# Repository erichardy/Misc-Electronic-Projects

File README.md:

# Misc-Electronic-Projects
Electronic circuits and projects I am working on as a hobbyist

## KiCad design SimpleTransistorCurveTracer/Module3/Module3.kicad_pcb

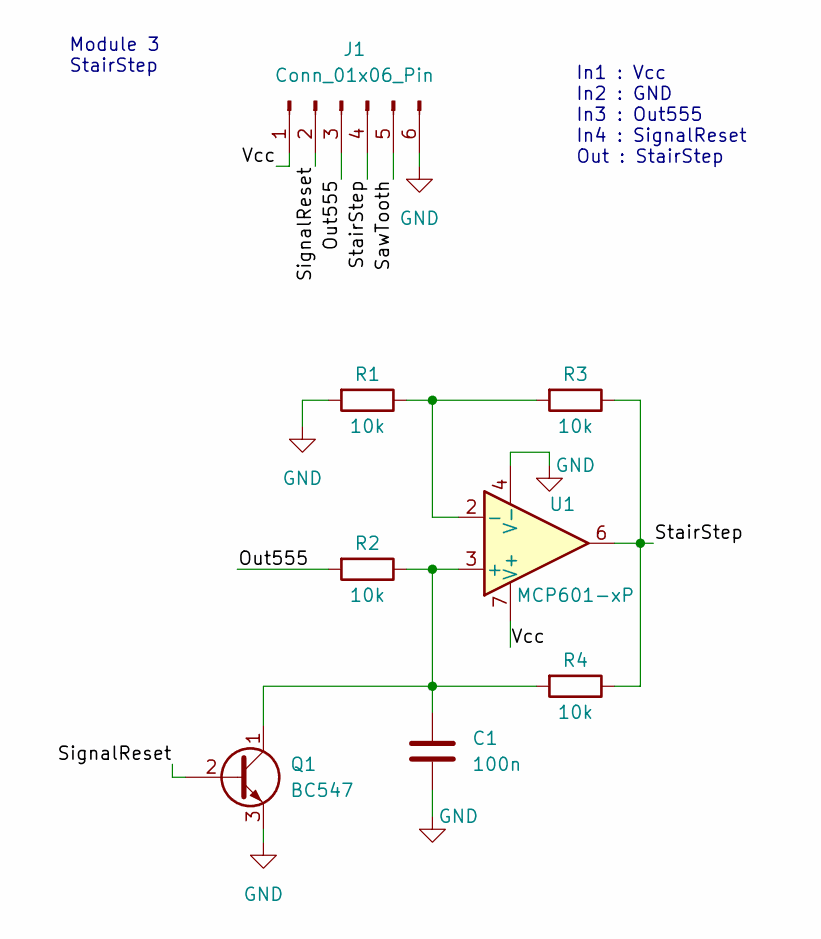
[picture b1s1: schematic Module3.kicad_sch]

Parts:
C1: 100n; C_Disc_D7.5mm_W2.5mm_P5.00mm
J1: Conn_01x06_Pin; PinHeader_1x06_P2.54mm_Horizontal
Q1: BC547; TO-92_Inline
R1, R2, R3, R4: 10k; R_Axial_DIN0411_L9.9mm_D3.6mm_P15.24mm_Horizontal
U1: MCP601-xP; DIP-8_W7.62mm

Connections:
/Out555: J1.3, R2.2
/SawTooth: J1.5
/SignalReset: J1.2, Q1.2 (B)
/StairStep: J1.4, R3.1, R4.1, U1.6
/Vcc: J1.1, U1.7 (V+)
GND: C1.2, J1.6, Q1.3 (E), R1.2, U1.4 (V-)
unnamed: C1.1, Q1.1 (C), R2.1, R4.2, U1.3 (+)
unnamed: R1.1, R3.2, U1.2 (-)

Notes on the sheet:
Module 3 StairStep
In1 : Vcc In2 : GND In3 : Out555 In4 : SignalReset Out : StairStep

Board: 2 copper layers, 8 parts (0 on the bottom side), 7 nets, no tracks yet.

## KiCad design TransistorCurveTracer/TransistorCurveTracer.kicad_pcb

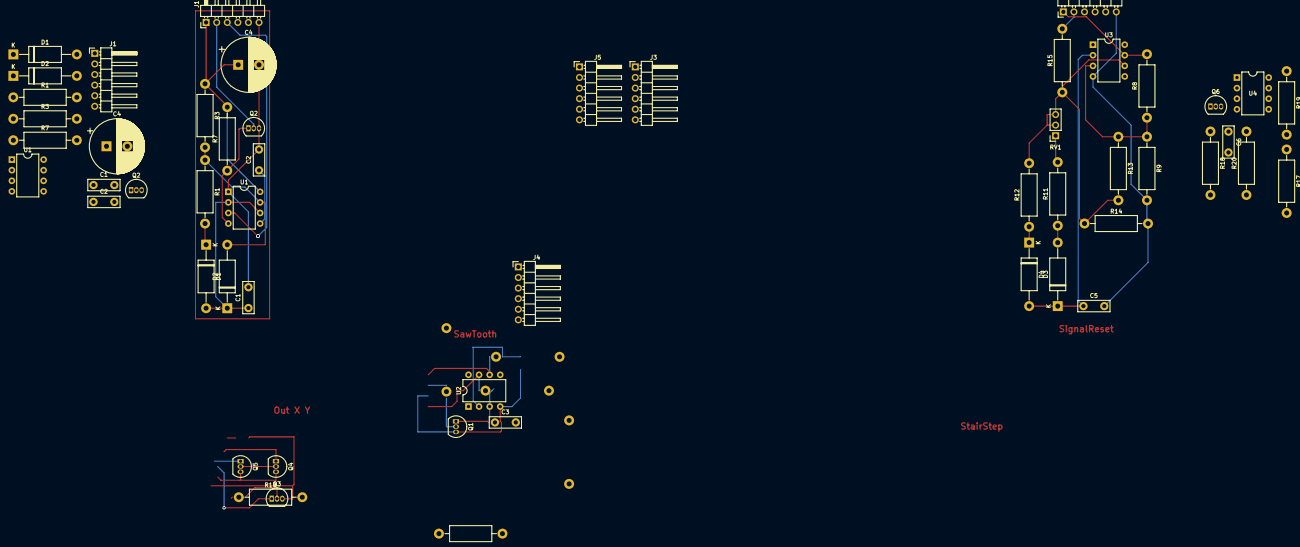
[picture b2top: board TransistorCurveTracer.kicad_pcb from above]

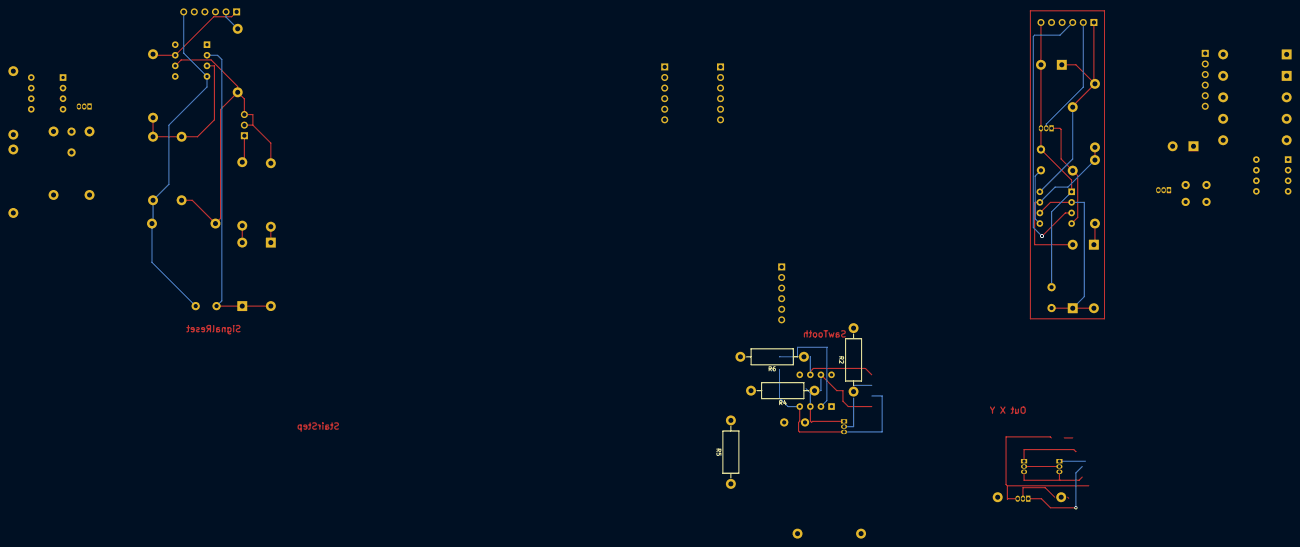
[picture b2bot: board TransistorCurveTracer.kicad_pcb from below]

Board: 2 copper layers, 57 parts (4 on the bottom side), 25 nets.

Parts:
C1, C1#2, C2, C2#2, C3: 10n; C_Disc_D7.5mm_W2.5mm_P5.00mm
C4, C4#2: 47u; CP_Radial_D13.0mm_P5.00mm
C5, C6: 100n; C_Disc_D7.5mm_W2.5mm_P5.00mm
D1, D1#2, D2, D2#2, D3, D4: 1N4148; D_DO-15_P15.24mm_Horizontal
J1, J1#2, J2, J3, J4, J5: Conn_01x06_Pin; PinHeader_1x06_P2.54mm_Horizontal
Q1, Q2, Q2#2, Q6: BC547; TO-92_Inline
Q3: DUT; TO-92_Inline
Q4, Q5: 2N2907; TO-92_Inline
R1, R1#2, R12: 39k; R_Axial_DIN0411_L9.9mm_D3.6mm_P15.24mm_Horizontal
R2, R5: 3.9k; R_Axial_DIN0411_L9.9mm_D3.6mm_P15.24mm_Horizontal
R3, R3#2: 4.7k; R_Axial_DIN0411_L9.9mm_D3.6mm_P15.24mm_Horizontal
R4, R6, R7, R7#2, R17, R18, R19, R20: 10k; R_Axial_DIN0411_L9.9mm_D3.6mm_P15.24mm_Horizontal
R8, R9: 33k; R_Axial_DIN0411_L9.9mm_D3.6mm_P15.24mm_Horizontal
R10: 470k; R_Axial_DIN0411_L9.9mm_D3.6mm_P15.24mm_Horizontal
R11: 1k; R_Axial_DIN0411_L9.9mm_D3.6mm_P15.24mm_Horizontal
R13: 15k; R_Axial_DIN0411_L9.9mm_D3.6mm_P15.24mm_Horizontal
R14: 6.8k; R_Axial_DIN0411_L9.9mm_D3.6mm_P15.24mm_Horizontal
R15: 8.2k; R_Axial_DIN0411_L9.9mm_D3.6mm_P15.24mm_Horizontal
R16: 270k; R_Axial_DIN0411_L9.9mm_D3.6mm_P15.24mm_Horizontal
RV1: 0-5k; PinSocket_1x03_P2.54mm_Vertical
U1, U1#2: NE555P; DIP-8_W7.62mm
U2, U3, U4: MCP601-xP; DIP-8_W7.62mm

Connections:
/Out555: J1.3, J1#2.3, J2.3, J3.3, J4.3, J5.3, R2.2, R18.2, U1.3 (Q), U1#2.3 (Q)
/Reset555: Q2.1 (C), Q2#2.1 (C), R7.1, R7#2.1, U1.4 (R), U1#2.4 (R)
/SawTooth: J1.5, J1#2.5, J2.5, J3.5, J4.5, J5.5, Q4.3 (E), Q5.3 (E), R6.1, U2.6
/SignalReset: J1.2, J1#2.2, J2.2, J3.2, J4.2, J5.2, Q2.2 (B), Q2#2.2 (B), Q6.2 (B), R15.2
/StairStep: J1.4, J1#2.4, J2.4, J3.4, J4.4, J5.4, R10.1, R19.1, R20.1, U4.6
/Vcc: C4.1, C4#2.1, J1.1, J1#2.1, J2.1, J3.1, J4.1, J5.1, R3.1, R3#2.1, R4.1, R7.2, R7#2.2, R8.2, U1.8 (VCC), U1#2.8 (VCC), U2.7 (V+), U3.7 (V+), U4.7 (V+)
/X: Q3.1 (C), Q4.1 (C), Q4.2 (B), Q5.2 (B)
/Y: Q5.1 (C), R16.1
GND: C1.2, C1#2.2, C2.2, C2#2.2, C3.2, C4.2, C4#2.2, C5.2, C6.2, J1.6, J1#2.6, J2.6, J3.6, J4.6, J5.6, Q1.3 (E), Q2.3 (E), Q2#2.3 (E), Q3.3 (E), Q6.3 (E), R5.2, R9.2, R14.2, R16.2, R17.2, U1.1 (GND), U1#2.1 (GND), U2.4 (V-), U3.4 (V-), U4.4 (V-)
unnamed: C1.1, C1#2.1, D1.2 (A), D1#2.2 (A), D2.1 (K), D2#2.1 (K), U1.2 (TR), U1.6 (THR), U1#2.2 (TR), U1#2.6 (THR)
unnamed: D1.1 (K), D1#2.1 (K), R1.2, R1#2.2
unnamed: D2.2 (A), D2#2.2 (A), R1.1, R1#2.1, R3.2, R3#2.2, U1.7 (DIS), U1#2.7 (DIS)
unnamed: D3.2 (A), R11.1
unnamed: C5.1, D3.1 (K), D4.2 (A), U3.2 (-)
unnamed: D4.1 (K), R12.1
unnamed: Q1.2 (B), R2.1
unnamed: C3.1, Q1.1 (C), R4.2, U2.3 (+)
unnamed: Q3.2 (B), R10.2
unnamed: C6.1, Q6.1 (C), R18.1, R20.2, U4.3 (+)
unnamed: R11.2, RV1.1
unnamed: R12.2, R13.2, R14.1, R15.1, RV1.2, RV1.3, U3.6
unnamed: C2.1, C2#2.1, U1.5 (CV), U1#2.5 (CV)
unnamed: R5.1, R6.2, U2.2 (-)
unnamed: R8.1, R9.1, R13.1, U3.3 (+)
unnamed: R17.1, R19.2, U4.2 (-)

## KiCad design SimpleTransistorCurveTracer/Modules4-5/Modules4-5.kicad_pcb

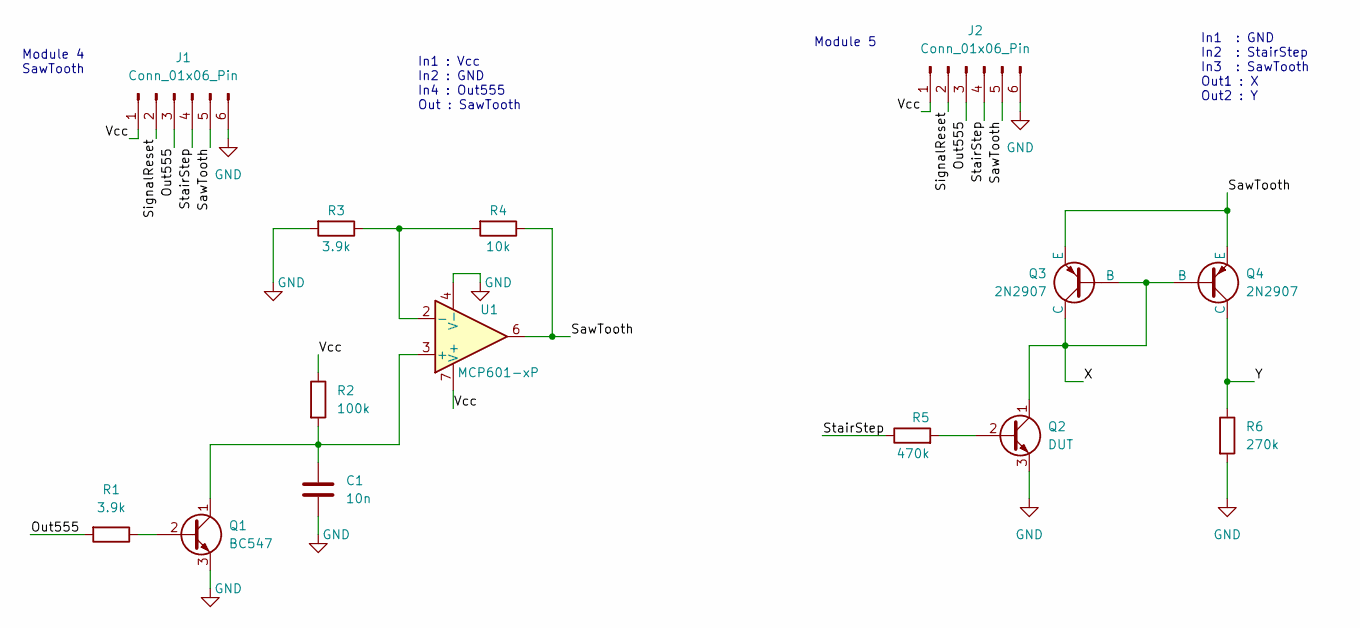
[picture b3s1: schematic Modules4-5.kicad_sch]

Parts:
C1: 10n; C_Disc_D7.5mm_W2.5mm_P5.00mm
J1, J2: Conn_01x06_Pin; PinHeader_1x06_P2.54mm_Horizontal
Q1: BC547; TO-92_Inline
Q2: DUT; TO-92_Inline
Q3, Q4: 2N2907; TO-92_Inline
R1, R3: 3.9k; R_Axial_DIN0411_L9.9mm_D3.6mm_P15.24mm_Horizontal
R2: 100k; R_Axial_DIN0411_L9.9mm_D3.6mm_P15.24mm_Horizontal
R4: 10k; R_Axial_DIN0411_L9.9mm_D3.6mm_P15.24mm_Horizontal
R5: 470k; R_Axial_DIN0411_L9.9mm_D3.6mm_P15.24mm_Horizontal
R6: 270k; R_Axial_DIN0411_L9.9mm_D3.6mm_P15.24mm_Horizontal
U1: MCP601-xP; DIP-8_W7.62mm

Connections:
/Out555: J1.3, J2.3, R1.2
/SawTooth: J1.5, J2.5, Q3.3 (E), Q4.3 (E), R4.1, U1.6
/SignalReset: J1.2, J2.2
/StairStep: J1.4, J2.4, R5.1
/Vcc: J1.1, J2.1, R2.1, U1.7 (V+)
/X: Q2.1 (C), Q3.1 (C), Q3.2 (B), Q4.2 (B)
/Y: Q4.1 (C), R6.1
GND: C1.2, J1.6, J2.6, Q1.3 (E), Q2.3 (E), R3.2, R6.2, U1.4 (V-)
unnamed: Q1.2 (B), R1.1
unnamed: C1.1, Q1.1 (C), R2.2, U1.3 (+)
unnamed: Q2.2 (B), R5.2
unnamed: R3.1, R4.2, U1.2 (-)

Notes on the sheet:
Module 5
Module 4 SawTooth
In1 : Vcc In2 : GND In4 : Out555 Out : SawTooth
In1 : GND In2 : StairStep In3 : SawTooth Out1 : X Out2 : Y

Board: 2 copper layers, 14 parts (0 on the bottom side), 12 nets, no tracks yet.

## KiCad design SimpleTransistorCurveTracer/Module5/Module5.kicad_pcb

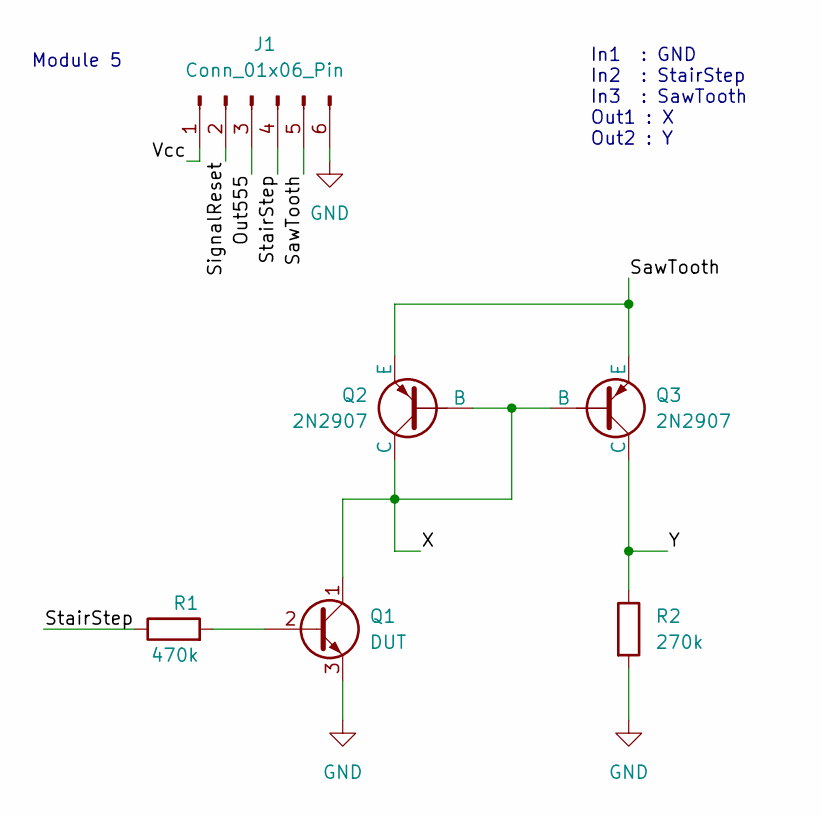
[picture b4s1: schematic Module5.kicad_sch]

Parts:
J1: Conn_01x06_Pin; PinHeader_1x06_P2.54mm_Horizontal
Q1: DUT; TO-92_Inline
Q2, Q3: 2N2907; TO-92_Inline
R1: 470k; R_Axial_DIN0411_L9.9mm_D3.6mm_P15.24mm_Horizontal
R2: 270k; R_Axial_DIN0411_L9.9mm_D3.6mm_P15.24mm_Horizontal

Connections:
/Out555: J1.3
/SawTooth: J1.5, Q2.3 (E), Q3.3 (E)
/SignalReset: J1.2
/StairStep: J1.4, R1.1
/Vcc: J1.1
/X: Q1.1 (C), Q2.1 (C), Q2.2 (B), Q3.2 (B)
/Y: Q3.1 (C), R2.1
GND: J1.6, Q1.3 (E), R2.2
unnamed: Q1.2 (B), R1.2

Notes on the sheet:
In1 : GND In2 : StairStep In3 : SawTooth Out1 : X Out2 : Y
Module 5

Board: 2 copper layers, 6 parts (0 on the bottom side), 6 nets, no tracks yet.

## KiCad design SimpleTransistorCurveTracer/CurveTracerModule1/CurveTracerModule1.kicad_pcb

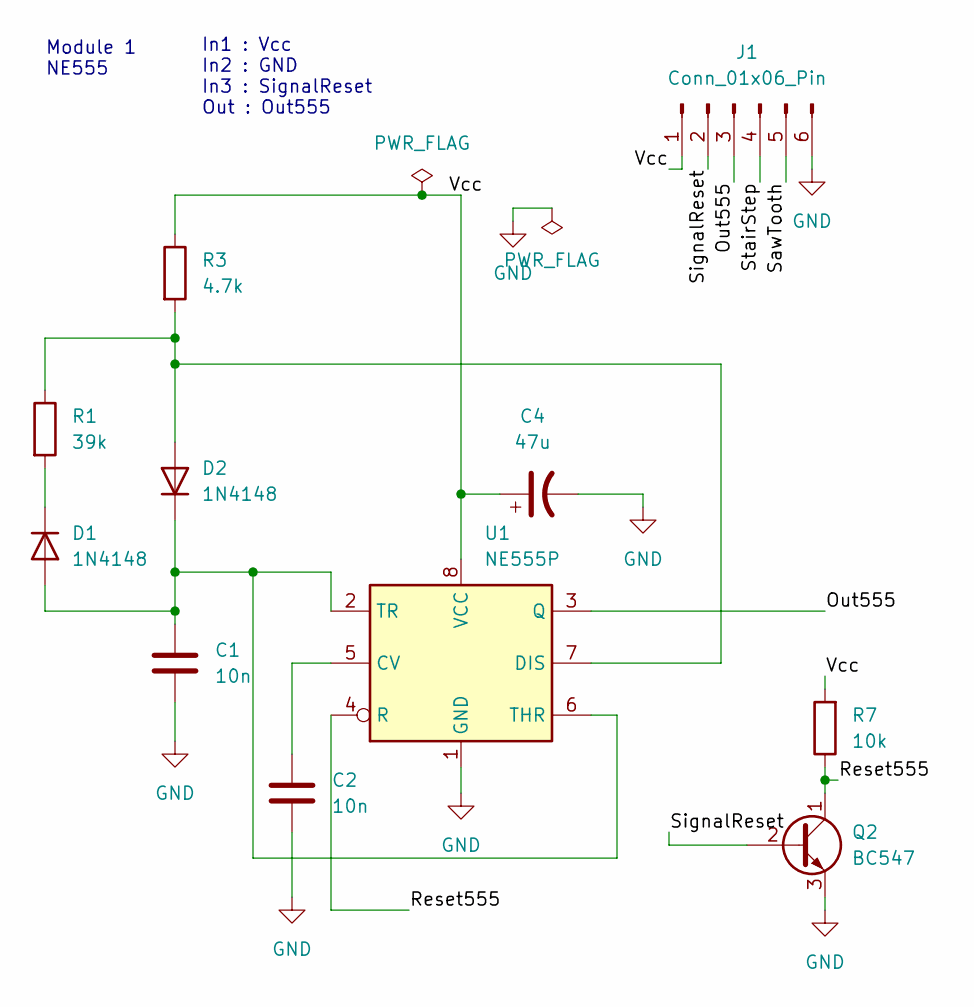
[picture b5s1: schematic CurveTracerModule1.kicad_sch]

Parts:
C1, C2: 10n; C_Disc_D7.5mm_W2.5mm_P5.00mm
C4: 47u; CP_Radial_D13.0mm_P5.00mm
D1, D2: 1N4148; D_DO-15_P15.24mm_Horizontal
J1: Conn_01x06_Pin; PinHeader_1x06_P2.54mm_Horizontal
Q2: BC547; TO-92_Inline
R1: 39k; R_Axial_DIN0411_L9.9mm_D3.6mm_P15.24mm_Horizontal
R3: 4.7k; R_Axial_DIN0411_L9.9mm_D3.6mm_P15.24mm_Horizontal
R7: 10k; R_Axial_DIN0411_L9.9mm_D3.6mm_P15.24mm_Horizontal
U1: NE555P; DIP-8_W7.62mm

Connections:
/Out555: J1.3, U1.3 (Q)
/Reset555: Q2.1 (C), R7.1, U1.4 (R)
/SawTooth: J1.5
/SignalReset: J1.2, Q2.2 (B)
/StairStep: J1.4
/Vcc: C4.1, J1.1, R3.1, R7.2, U1.8 (VCC)
GND: C1.2, C2.2, C4.2, J1.6, Q2.3 (E), U1.1 (GND)
unnamed: C1.1, D1.2 (A), D2.1 (K), U1.2 (TR), U1.6 (THR)
unnamed: D1.1 (K), R1.2
unnamed: D2.2 (A), R1.1, R3.2, U1.7 (DIS)
unnamed: C2.1, U1.5 (CV)

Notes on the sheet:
In1 : Vcc In2 : GND In3 : SignalReset Out : Out555
Module 1 NE555

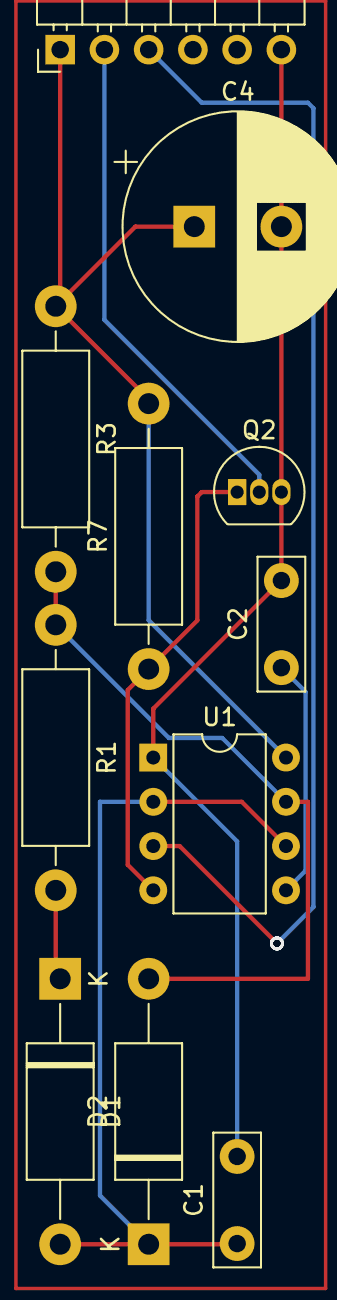
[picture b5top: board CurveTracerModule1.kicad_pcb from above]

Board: 2 copper layers, 11 parts (0 on the bottom side), 9 nets.

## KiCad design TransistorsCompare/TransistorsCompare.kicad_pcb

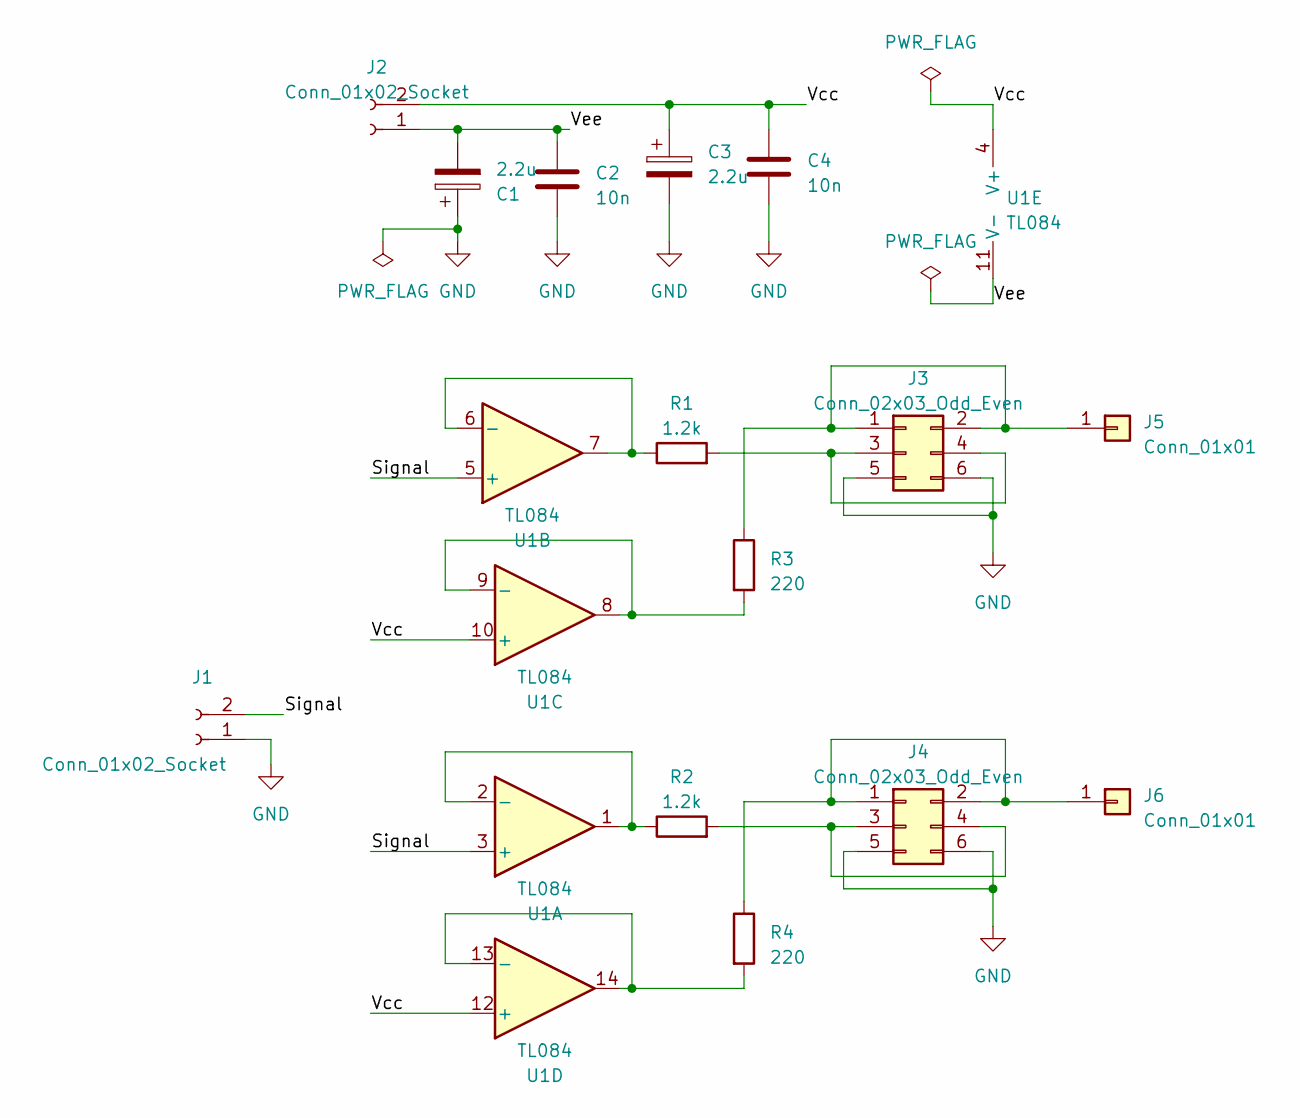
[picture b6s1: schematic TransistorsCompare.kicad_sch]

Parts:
C1, C3: 2.2u; C_Radial_D6.3mm_H5.0mm_P2.50mm
C2, C4: 10n; C_Disc_D5.0mm_W2.5mm_P2.50mm
J1, J2: Conn_01x02_Socket; PinSocket_1x02_P2.54mm_Vertical
J3, J4: Conn_02x03_Odd_Even; PinSocket_2x03_P2.54mm_Vertical
J5, J6: Conn_01x01; PinHeader_1x01_P2.54mm_Vertical
R1, R2: 1.2k; R_Axial_DIN0207_L6.3mm_D2.5mm_P10.16mm_Horizontal
R3, R4: 220; R_Axial_DIN0207_L6.3mm_D2.5mm_P10.16mm_Horizontal
U1: TL084; DIP-14_W7.62mm_Socket

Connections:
/Signal: J1.2, U1.3 (+), U1.5 (+)
/Vcc: C3.1, C4.1, J2.2, U1.4 (V+), U1.10 (+), U1.12 (+)
/Vee: C1.2, C2.1, J2.1, U1.11 (V-)
GND: C1.1, C2.2, C3.2, C4.2, J1.1, J3.5, J3.6, J4.5, J4.6
unnamed: J3.1, J3.2, J5.1, R3.1
unnamed: J3.3, J3.4, R1.2
unnamed: J4.1, J4.2, J6.1, R4.1
unnamed: J4.3, J4.4, R2.2
unnamed: R2.1, U1.1, U1.2 (-)
unnamed: R1.1, U1.6 (-), U1.7
unnamed: R3.2, U1.8, U1.9 (-)
unnamed: R4.2, U1.13 (-), U1.14

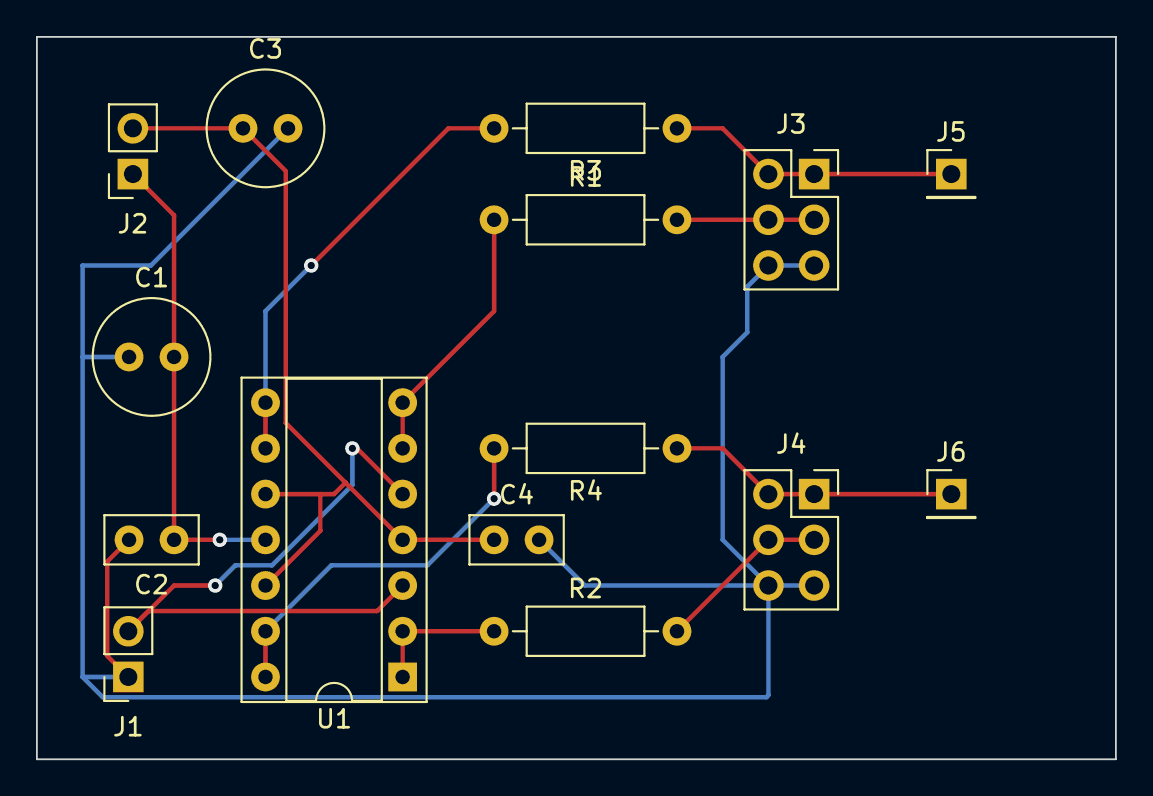
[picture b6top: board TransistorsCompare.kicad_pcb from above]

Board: 2 copper layers, 59.9 x 40.1 mm, 15 parts (0 on the bottom side), 12 nets.

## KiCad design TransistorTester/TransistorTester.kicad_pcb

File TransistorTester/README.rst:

One of my prefered electronic youtuber is w2aew (https://www.youtube.com/@w2aew) and this
circuit is from his video named :
 #281: Bipolar Transistor Switching Time Measurement
 (https://www.youtube.com/watch?v=XgSKLsWAWGs&ab_channel=w2aew)

A friend of mine gave me a lot of parts including transistors and I plan to use this
circuit to help me to test transistors as well those I buy either in China or at
specialised resellers... and to compare them...

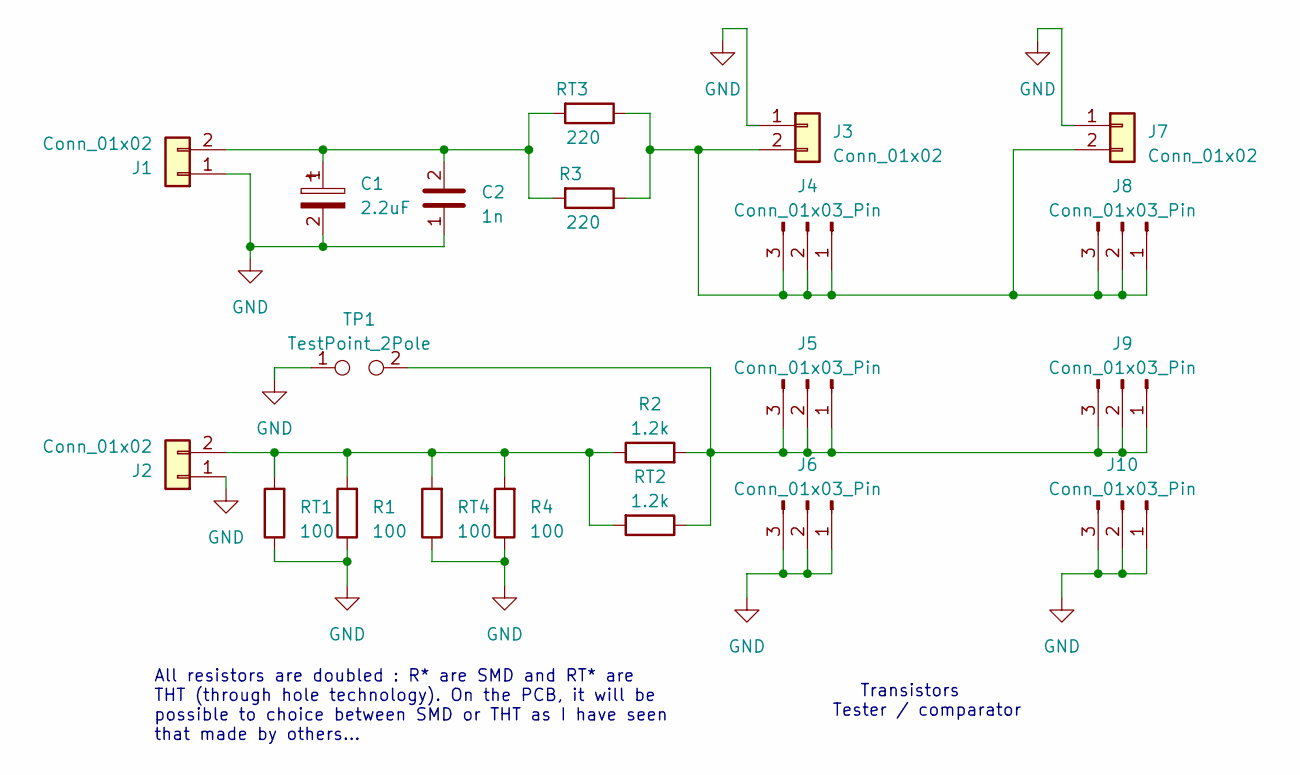
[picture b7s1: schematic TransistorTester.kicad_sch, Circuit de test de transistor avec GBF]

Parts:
C1: 2.2uF; CP_Radial_D4.0mm_P1.50mm
C2: 1n; C_Disc_D3.0mm_W1.6mm_P2.50mm
J1, J2, J3, J7: Conn_01x02; PinHeader_1x02_P2.54mm_Vertical
J4, J5, J6, J8, J9, J10: Conn_01x03_Pin; PinSocket_1x03_P2.54mm_Vertical
R1, R4: 100; R_0805_2012Metric_Pad1.20x1.40mm_HandSolder
R2: 1.2k; R_0805_2012Metric_Pad1.20x1.40mm_HandSolder
R3: 220; R_0805_2012Metric_Pad1.20x1.40mm_HandSolder
RT1, RT4: 100; R_Axial_DIN0411_L9.9mm_D3.6mm_P12.70mm_Horizontal
RT2: 1.2k; R_Axial_DIN0411_L9.9mm_D3.6mm_P12.70mm_Horizontal
RT3: 220; R_Axial_DIN0411_L9.9mm_D3.6mm_P12.70mm_Horizontal
TP1: TestPoint_2Pole; PinHeader_1x02_P2.54mm_Vertical

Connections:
GND: C1.2, C2.1, J1.1, J2.1, J3.1, J6.1, J6.2, J6.3, J7.1, J10.1, J10.2, J10.3, R1.1, R4.1, RT1.1, RT4.1, TP1.1
unnamed: C1.1, C2.2, J1.2, R3.2, RT3.2
unnamed: J2.2, R1.2, R2.1, R4.2, RT1.2, RT2.2, RT4.2
unnamed: J3.2, J4.1, J4.2, J4.3, J7.2, J8.1, J8.2, J8.3, R3.1, RT3.1
unnamed: J5.1, J5.2, J5.3, J9.1, J9.2, J9.3, R2.2, RT2.1, TP1.2

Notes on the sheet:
Transistors Tester / comparator
All resistors are doubled : R* are SMD and RT* are THT (through hole technology). On the PCB, it will be possible to choice between SMD or THT as I have seen that made by others...

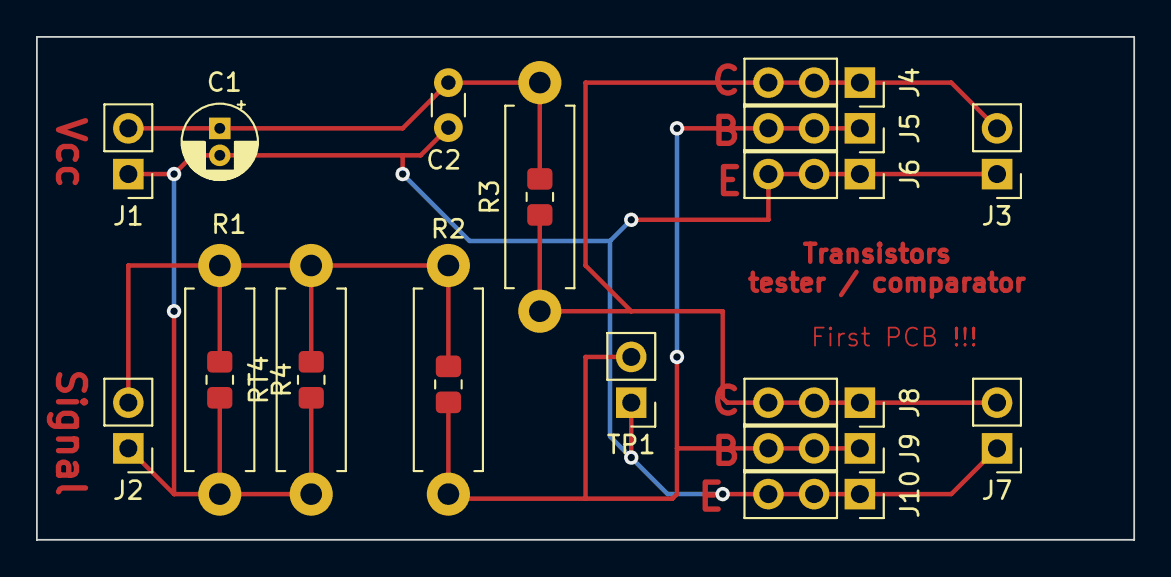
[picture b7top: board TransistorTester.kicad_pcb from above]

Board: 2 copper layers, 61.0 x 27.9 mm, 21 parts (0 on the bottom side), 5 nets.

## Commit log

2023-04-26 add TransistorTester project
2023-04-26 fix resistors
2023-04-26 add .gitignore
2023-04-27 adapt to board
2023-05-02 TransistorsCompare
2023-05-09 fix : all thrue one AOP
2023-05-25 T compare
2023-08-14 TransistorCurveTracer in progress
2023-08-14 in progress
2023-08-18 curve tracer in progress
2023-08-19 fix .gitignore
2023-08-19 fix VCC/GND VDD/VSS in progress
2023-08-30 fixes
2023-09-18 5 modules
2023-09-24 cleanup
2023-09-24 imgs
2024-01-16 first commit for HomeSensors
2024-01-20 tests in progress
2024-01-23 HomeSensors in progress
2024-01-23 add ovenTemperture project
2024-01-28 ovenTemp in progress
2024-04-02 heartSensor
2024-04-02 minor changes
